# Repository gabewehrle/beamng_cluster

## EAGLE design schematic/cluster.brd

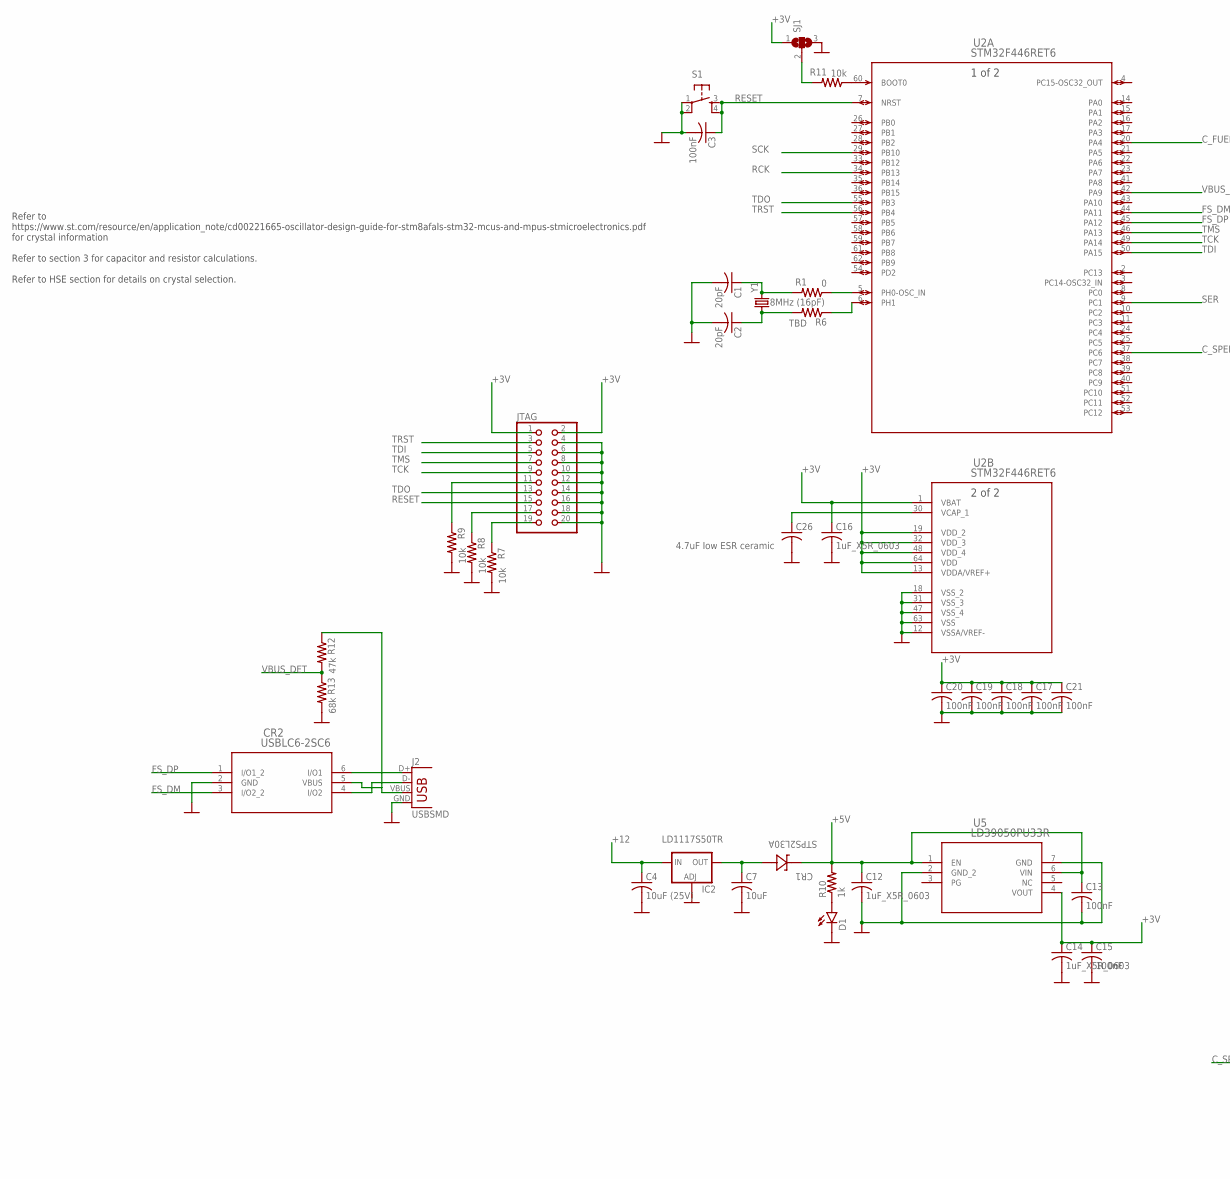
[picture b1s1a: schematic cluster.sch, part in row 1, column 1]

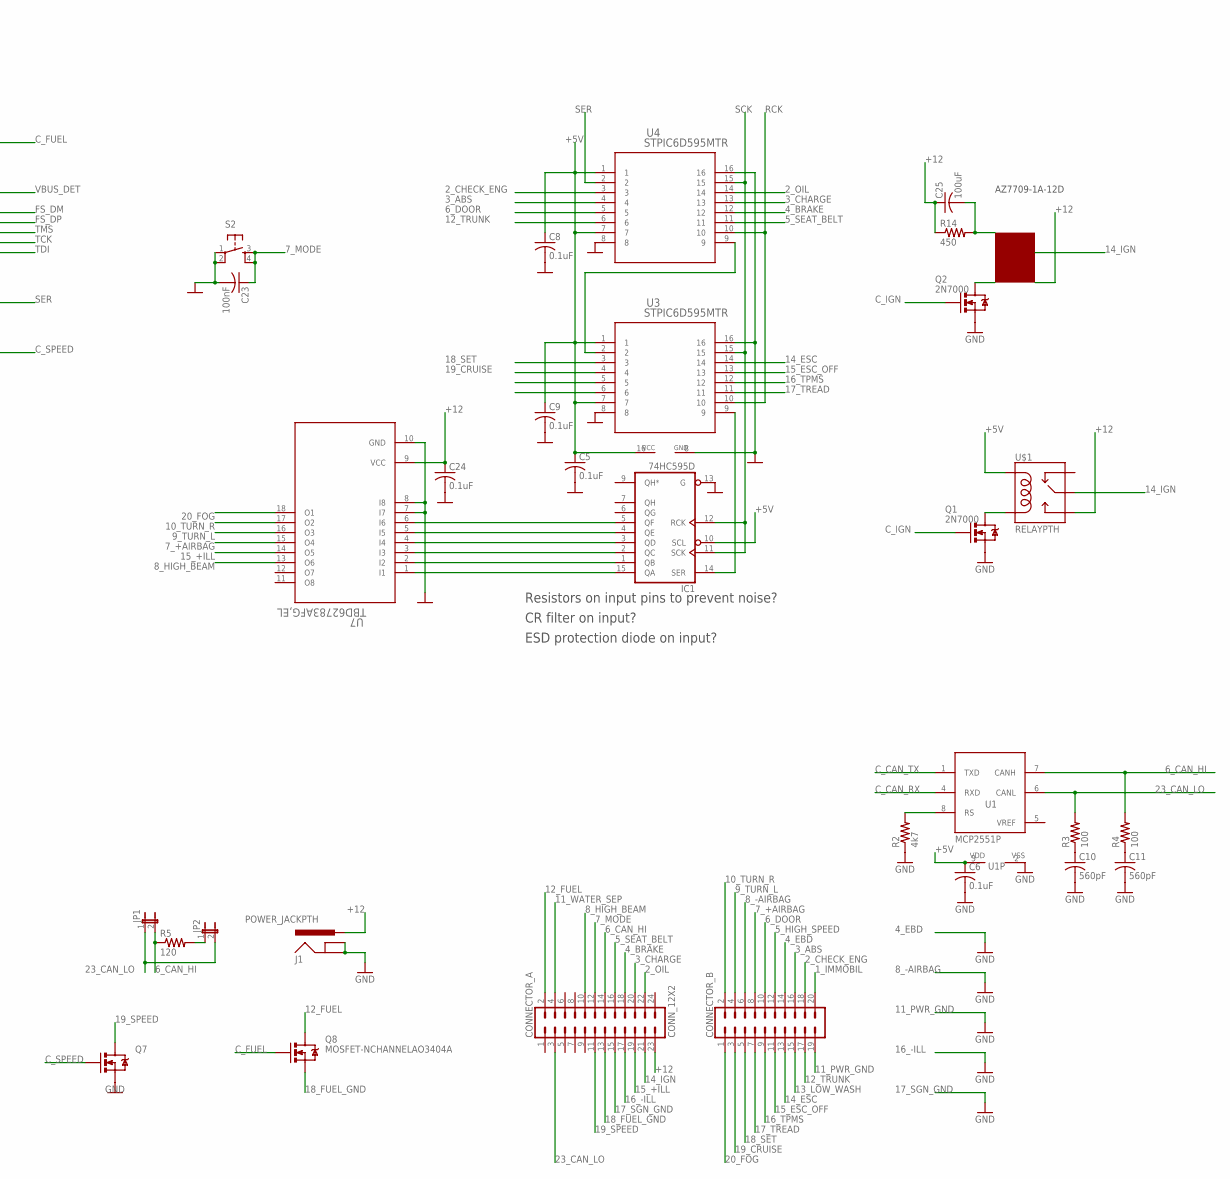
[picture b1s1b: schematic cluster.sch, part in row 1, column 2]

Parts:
C1, C2: 20pF; C0805K
C3, C13, C15, C17, C18, C19, C20, C21, C23: 100nF; C0805K
C4: 10uF (25V); C0805K
C5, C6, C8, C9, C24: 0.1uF; C0805K
C7: 10uF; C0805K
C10, C11: 560pF; C0805K
C12, C14, C16: 1uF_X5R_0603; C0805K
C25: 100uF; C0805K
C26: 4.7uF low ESR ceramic; C1206K
CONNECTOR_A: CONN_12X2; 2X12
CONNECTOR_B: CONN_10X2NOSILK; 2X10_NOSILK
CR1: STPS2L30A; SMA_STM
CR2: USBLC6-2SC6; SOT23-6L_STM
D1: LED-FKIT-1206; FKIT-LED-1206
IC1: 74HC595D; SO16
IC2: LD117AS12TR; SOT223
J1: POWER_JACKPTH; POWER_JACK_PTH
J2: USBSMD; USB-MINIB
JP1, JP2: JP1E; JP1
JTAG: PINHD-2X10; 2X10
Q1, Q2: 2N7000; SOT23-3
Q7, Q8: MOSFET-NCHANNELAO3404A; SOT23-3
R1: 0; R0805
R2: 4k7; R0805
R3, R4: 100; R0805
R5: 120; R0805
R6: TBD; R0805
R7, R8, R9, R11: 10k; R0805
R10: 1k; R0805
R12: 47k; R0805
R13: 68k; R0805
R14: 450; R0805
S1, S2: TAC_SWITCHPTH; TACTILE-PTH
SJ1: SJ2WW; SJ_2W
U1: MCP2551P; DIL8
U2: STM32F446RET6; LQFP64-10X10MM
U3, U4: STPIC6D595MTR; SO16_STPIC6D595MTR_STM
U5: LD39050PU33R; DFN6_3X3_STM
U7: TBD62783AFG,EL; SOP18-P-375-1P27_TOS
U$1: RELAYPTH; SRD-05VDC-SL-C
Y1: 8MHz (16pF); HC49US

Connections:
1_IMMOBIL: CONNECTOR_B.20
2_CHECK_ENG: CONNECTOR_B.18, U4.3
2_OIL: CONNECTOR_A.22, U4.14
3_ABS: CONNECTOR_B.16, U4.4
3_CHARGE: CONNECTOR_A.20, U4.13
4_BRAKE: CONNECTOR_A.18, U4.12
4_EBD: CONNECTOR_B.14
5_HIGH_SPEED: CONNECTOR_B.12
5_SEAT_BELT: CONNECTOR_A.16, U4.11
6_CAN_HI: CONNECTOR_A.14, JP1.2, R4.2, R5.1, U1.7 (CANH)
6_DOOR: CONNECTOR_B.10, U4.5
7_+AIRBAG: CONNECTOR_B.8, U7.15 (O4)
7_MODE: C23.1, CONNECTOR_A.12, S2.3, S2.4
8_-AIRBAG: CONNECTOR_B.6
8_HIGH_BEAM: CONNECTOR_A.10, U7.13 (O6)
9_TURN_L: CONNECTOR_B.4, U7.16 (O3)
10_TURN_R: CONNECTOR_B.2, U7.17 (O2)
11_PWR_GND: CONNECTOR_B.19
11_WATER_SEP: CONNECTOR_A.4
12_FUEL: CONNECTOR_A.2, Q8.3 (D)
12_TRUNK: CONNECTOR_B.17, U4.6
13_LOW_WASH: CONNECTOR_B.15
14_ESC: CONNECTOR_B.13, U3.14
14_IGN: CONNECTOR_A.21, U$1.SWCOMMON
15_+ILL: CONNECTOR_A.19, U7.14 (O5)
15_ESC_OFF: CONNECTOR_B.11, U3.13
16_-ILL: CONNECTOR_A.17
16_TPMS: CONNECTOR_B.9, U3.12
17_SGN_GND: CONNECTOR_A.15
17_TREAD: CONNECTOR_B.7, U3.11
18_FUEL_GND: CONNECTOR_A.13, Q8.2 (S)
18_SET: CONNECTOR_B.5, U3.3
19_CRUISE: CONNECTOR_B.3, U3.4
19_SPEED: CONNECTOR_A.11, Q7.3 (D)
20_FOG: CONNECTOR_B.1, U7.18 (O1)
23_CAN_LO: CONNECTOR_A.3, JP1.1, JP2.2, R3.2, U1.6 (CANL)
+3V: C14.1, C15.1, C16.1, C17.1, C18.1, C19.1, C20.1, C21.1, JTAG.1, JTAG.2, SJ1.1, U2.1 (VBAT), U2.13 (VDDA/VREF+), U2.19 (VDD_2), U2.32 (VDD_3), U2.48 (VDD_4), U2.64 (VDD), U5.4 (VOUT)
+5V: C5.1, C6.1, C8.1, C9.1, C12.1, C13.1, CR1.2 (A), IC1.10 (SCL), IC1.16 (VCC), R10.2, U1.3 (VDD), U3.1, U3.7, U4.1, U4.7, U5.1 (EN), U5.6 (VIN), U$1.COIL1
+12: C4.1, C24.1, C25.1, CONNECTOR_A.23, IC2.3 (IN), J1.PWR, R14.1, U7.9 (VCC), U$1.SWOPEN
C_CAN_RX: U1.4 (RXD)
C_CAN_TX: U1.1 (TXD)
C_FUEL: Q8.1 (G), U2.20 (PA4)
C_IGN: Q1.1 (G), Q2.1 (G)
C_SPEED: Q7.1 (G), U2.37 (PC6)
FS_DM: CR2.3 (I/O2_2), U2.44 (PA11)
FS_DP: CR2.1 (I/O1_2), U2.45 (PA12)
GND: C1.2, C2.2, C3.2, C4.2, C5.2, C6.2, C7.2, C8.2, C9.2, C10.2, C11.2, C12.2, C13.2, C14.2, C15.2, C16.2, C17.2, C18.2, C19.2, C20.2, C21.2, C23.2, C24.2, C26.2, CR2.2 (GND), D1.C, IC1.8 (GND), IC1.13 (G), IC2.1 (ADJ), J1.GND, J1.GNDBREAK, J2.GND, JTAG.4, JTAG.6, JTAG.8, JTAG.10, JTAG.12, JTAG.14, JTAG.16, JTAG.18, JTAG.20, Q1.2 (S), Q2.2 (S), Q7.2 (S), R2.1, R7.2, R8.2, R9.2, R13.2, S1.1, S1.2, S2.1, S2.2, SJ1.3, U1.2 (VSS), U2.12 (VSSA/VREF-), U2.18 (VSS_2), U2.31 (VSS_3), U2.47 (VSS_4), U2.63 (VSS), U3.8, U3.16, U4.8, U4.16, U5.2 (GND_2), U5.7 (GND), U7.7 (I7), U7.8 (I8), U7.10 (GND)
unnamed: U3.2, U4.9
unnamed: IC1.14 (SER), U3.9
unnamed: IC1.15 (QA), U7.1 (I1)
unnamed: IC1.1 (QB), U7.2 (I2)
unnamed: IC1.2 (QC), U7.3 (I3)
unnamed: C7.1, CR1.1 (K), IC2.4 (OUT)
unnamed: JP2.1, R5.2
unnamed: R2.2, U1.8 (RS)
unnamed: IC1.3 (QD), U7.4 (I4)
unnamed: IC1.4 (QE), U7.5 (I5)
unnamed: C10.1, R3.1
unnamed: C11.1, R4.1
unnamed: IC1.5 (QF), U7.6 (I6)
unnamed: R1.1, U2.5 (PH0-OSC_IN)
unnamed: R6.1, U2.6 (PH1)
unnamed: C1.1, R1.2, Y1.2
unnamed: C2.1, R6.2, Y1.1
unnamed: JTAG.19, R7.1
unnamed: JTAG.17, R8.1
unnamed: JTAG.11, R9.1
unnamed: D1.A, R10.1
unnamed: C25.2, R14.2
unnamed: C26.1, U2.30 (VCAP_1)
unnamed: R11.1, U2.60 (BOOT0)
unnamed: R11.2, SJ1.2
unnamed: CR2.6 (I/O1), J2.D+
unnamed: CR2.4 (I/O2), J2.D-
unnamed: CR2.5 (VBUS), J2.VBUS, R12.1
unnamed: Q1.3 (D), U$1.COIL0
PG: U5.3 (PG)
RCK: U2.34 (PB13), U3.10, U4.10
RESET: C3.1, JTAG.15, S1.3, S1.4, U2.7 (NRST)
SCK: IC1.11 (SCK), IC1.12 (RCK), U2.29 (PB10), U3.15, U4.15
SER: U2.9 (PC1), U4.2
TCK: JTAG.9, U2.49 (PA14)
TDI: JTAG.5, U2.50 (PA15)
TDO: JTAG.13, U2.55 (PB3)
TMS: JTAG.7, U2.46 (PA13)
TRST: JTAG.3, U2.56 (PB4)
VBUS_DET: R12.2, R13.1, U2.42 (PA9)
VREF: U1.5 (VREF)

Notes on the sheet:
Refer to https://www.st.com/resource/en/application_note/cd00221665-oscillator-design-guide-for-stm8afals-stm32-mcus-and-mpus-stmicroelectronics.pdf for crystal information Refer to section 3 for capacitor and resistor calculations. Refer to HSE section for details on crystal selection.
LD1117S50TR
Resistors on input pins to prevent noise?
CR filter on input?
ESD protection diode on input?
AZ7709-1A-12D

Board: 2 copper layers, 66 parts (1 on the bottom side), 75 nets, no tracks yet.

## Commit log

2021-08-14 Uploaded files
2021-08-14 Uploaded Arduino Due sketch
2021-11-29 Upload compiled exe
2021-11-29 Now accepts port number as command line arg

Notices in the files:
parts and their libraries:
SparkFun-Connectors: Licensing: Creative Commons ShareAlike 4.0 International - https://creativecommons.org/licenses/by-sa/4.0
COPYRIGHT: Copyright (C) 2018 Accelerated Designs. All rights reserved
